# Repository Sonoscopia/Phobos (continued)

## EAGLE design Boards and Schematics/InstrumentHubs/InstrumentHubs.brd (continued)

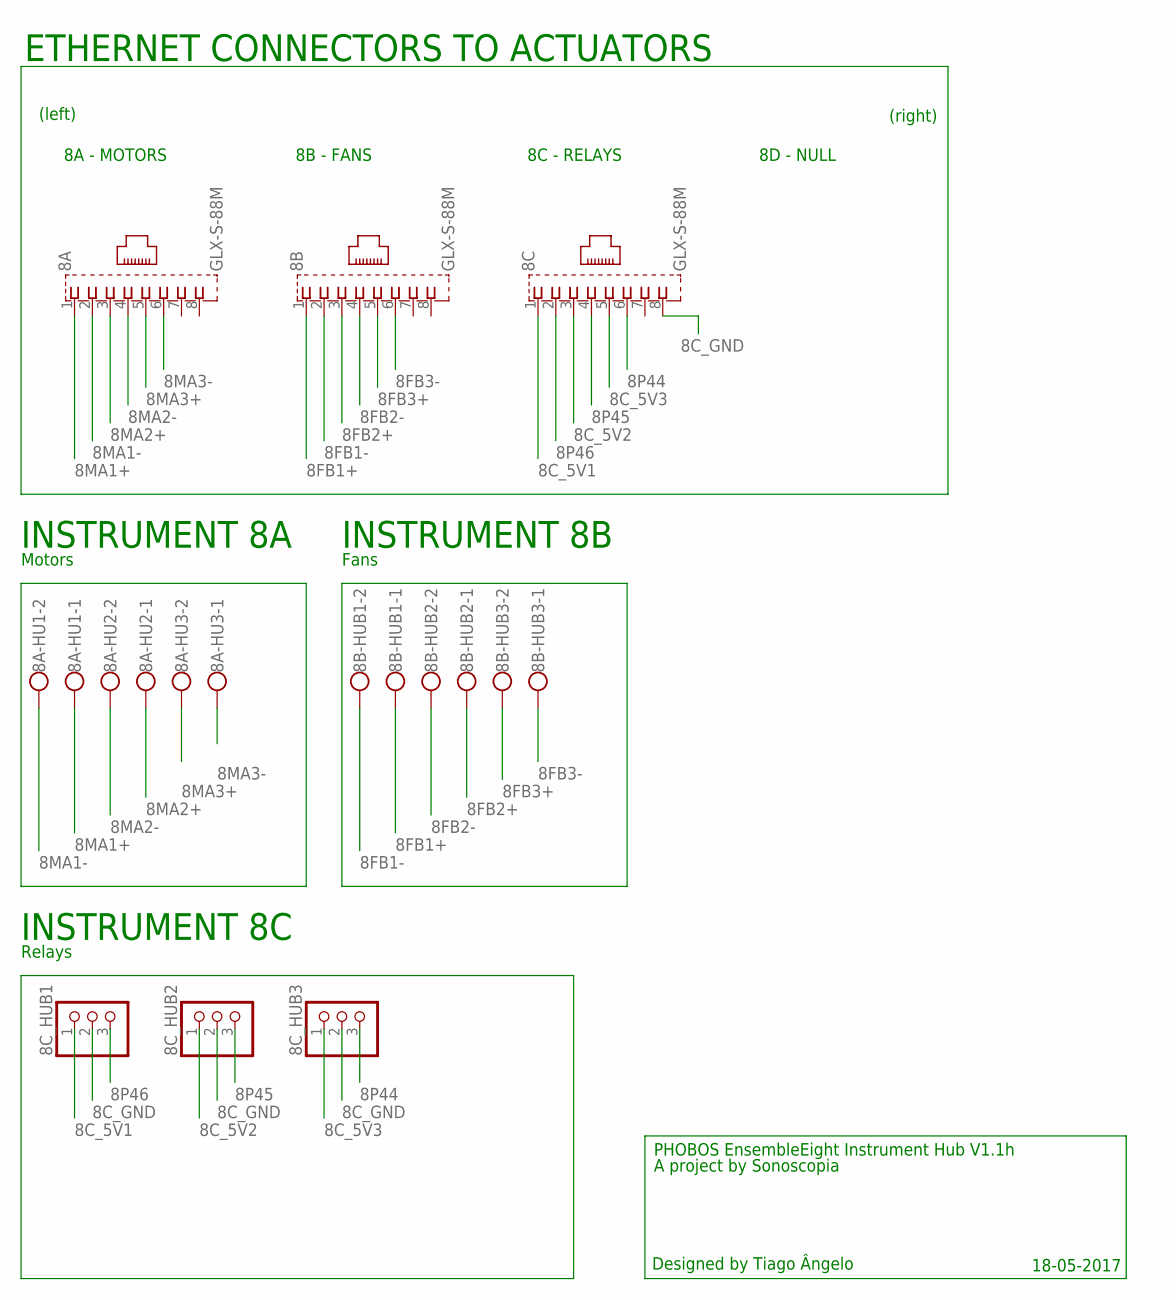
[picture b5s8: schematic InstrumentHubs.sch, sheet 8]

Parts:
8A, 8B, 8C: GLX-S-88M
8A-HU1, 8A-HU2, 8A-HU3, 8B-HUB1, 8B-HUB2, 8B-HUB3: W237-102
8C_HUB1, 8C_HUB2, 8C_HUB3: PINHD-1X3; 1X03

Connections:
8C_5V1: 8C.1, 8C_HUB1.1
8C_5V2: 8C.3, 8C_HUB2.1
8C_5V3: 8C.5, 8C_HUB3.1
8C_GND: 8C.8, 8C_HUB1.2, 8C_HUB2.2, 8C_HUB3.2
8FB1+: 8B.1, 8B-HUB1.1
8FB1-: 8B.2, 8B-HUB1.2
8FB2+: 8B.3, 8B-HUB2.1
8FB2-: 8B.4, 8B-HUB2.2
8FB3+: 8B.5, 8B-HUB3.2
8FB3-: 8B.6, 8B-HUB3.1
8MA1+: 8A.1, 8A-HU1.1
8MA1-: 8A.2, 8A-HU1.2
8MA2+: 8A.3, 8A-HU2.1
8MA2-: 8A.4, 8A-HU2.2
8MA3+: 8A.5, 8A-HU3.2
8MA3-: 8A.6, 8A-HU3.1
8P44: 8C.6, 8C_HUB3.3
8P45: 8C.4, 8C_HUB2.3
8P46: 8C.2, 8C_HUB1.3

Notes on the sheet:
INSTRUMENT 8A
PHOBOS EnsembleEight Instrument Hub V1.1h
Designed by Tiago Ângelo
A project by Sonoscopia
18-05-2017
Motors
INSTRUMENT 8B
Fans
INSTRUMENT 8C
Relays
(right)
(left)
ETHERNET CONNECTORS TO ACTUATORS
8D - NULL
8C - RELAYS
8B - FANS
8A - MOTORS

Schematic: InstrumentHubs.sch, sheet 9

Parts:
9A, 9B: GLX-S-88M
9A-HUB1, 9A-HUB2, 9A-HUB3, 9A-HUB4, 9B-HUB1, 9B-HUB2, 9B-HUB3: W237-102

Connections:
9LA1+: 9A.1, 9A-HUB1.1
9LA1-: 9A.2, 9A-HUB1.2
9LA2+: 9A.3, 9A-HUB2.1
9LA2-: 9A.4, 9A-HUB2.2
9LA3+: 9A.5, 9A-HUB3.2
9LA3-: 9A.6, 9A-HUB3.1
9LA4+: 9A.7, 9A-HUB4.2
9LA4-: 9A.8, 9A-HUB4.1
9LB1+: 9B.1, 9B-HUB1.1
9LB1-: 9B.2, 9B-HUB1.2
9LB2+: 9B.3, 9B-HUB2.1
9LB2-: 9B.4, 9B-HUB2.2
9LB3+: 9B.5, 9B-HUB3.2
9LB3-: 9B.6, 9B-HUB3.1

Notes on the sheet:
INSTRUMENT 9A
PHOBOS EnsembleNine Instrument Hub V1.1h
Designed by Tiago Ângelo
A project by Sonoscopia
Solenoid_valves_1
INSTRUMENT 9B
Solenoids_valves_2
18-05-2017
(right)
(left)
ETHERNET CONNECTORS TO ACTUATORS
9D - NULL
9C - NULL
9B - SOLENOIDS_VALVES_2
9A - SOLENOIDS_VALVES_1

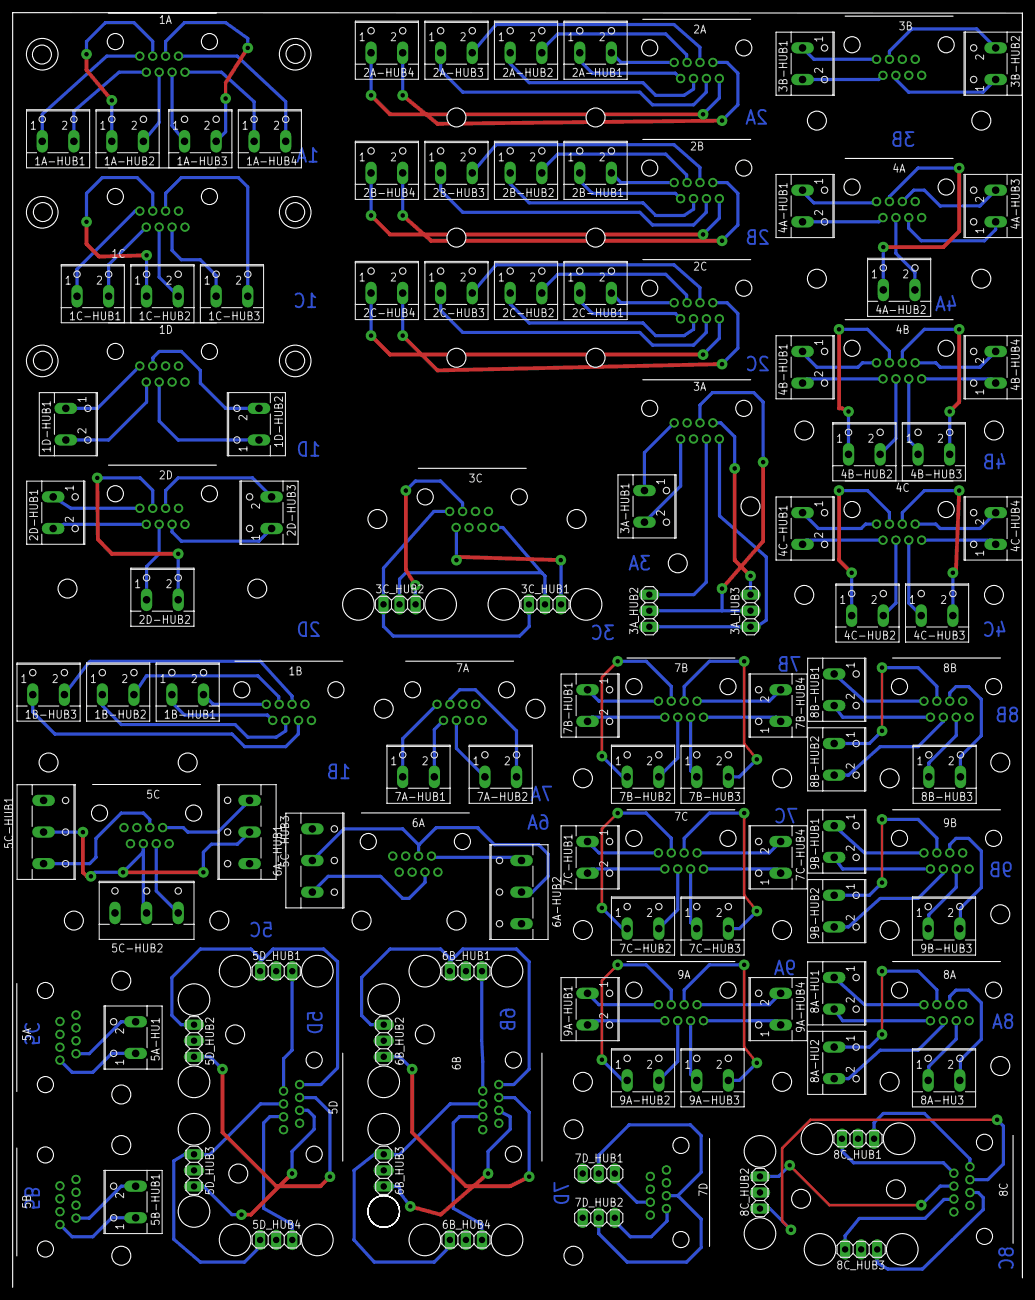
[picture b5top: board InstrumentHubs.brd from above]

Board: 2 copper layers, 159.7 x 201.6 mm, 117 parts (0 on the bottom side), 174 nets.

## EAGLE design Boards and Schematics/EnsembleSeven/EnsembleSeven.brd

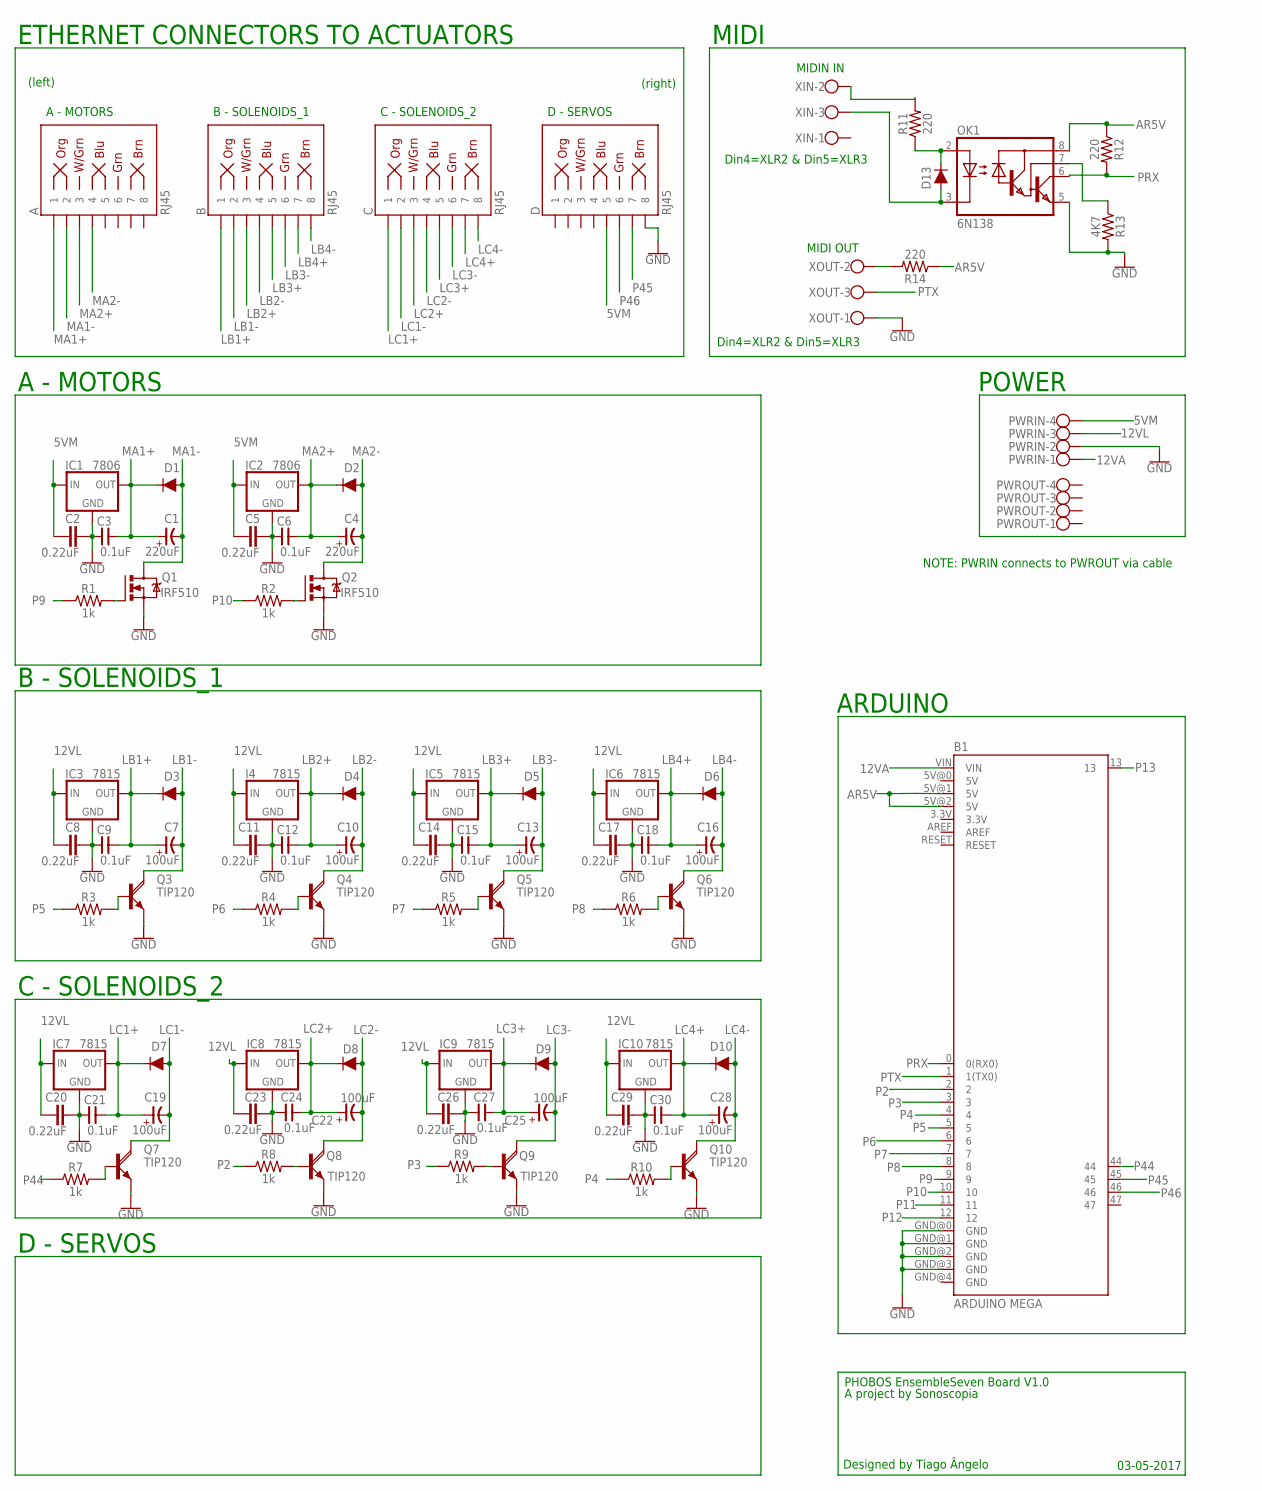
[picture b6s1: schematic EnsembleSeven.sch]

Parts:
A: RJ45; RJ45-8
B: RJ45; RJ45-8
B1: ARDUINO MEGA; ARDUINO_MEGA
C: RJ45; RJ45-8
C1, C4: 220uF; E-035X080
C2, C5, C8, C11, C14, C17, C20, C23, C26, C29: 0.22uF; C5B3
C3, C6, C9, C12, C15, C18, C21, C24, C27, C30: 0.1uF; C025-050X025
C7, C10, C13, C16, C19, C28: 100uF; CAP-MASTER_E-020X050
C22, C25: 100uF; E-020X050
D: RJ45; RJ45-8
D1, D2, D3, D4, D5, D6, D7, D8, D9, D10: 1A/50V/1.1V; DIODE-1N4001-KIT
D13: 200mA/100V/1V; DIODE-1N4148
I4: 7815; 78XXS
IC1, IC2: 7806; 78XXS
IC3, IC5, IC6, IC7, IC8, IC9, IC10: 7815; 78XXS
OK1: 6N138; DIL08
PWRIN: W237-4
PWROUT: W237-4
Q1, Q2: IRF510; TO220BV
Q3, Q4, Q5, Q6, Q7, Q10: TIP120; ROCKETFARM_TO220AV
Q8, Q9: TIP120; TO220AV
R1, R2, R3, R4, R5, R6, R7, R8, R9, R10: 1k; AXIAL-0.1
R11, R12, R14: 220; AXIAL-0.3
R13: 4K7; AXIAL-0.3
XIN: W237-103
XOUT: W237-103

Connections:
5VM: C2.1, C5.1, D.5, IC1.IN, IC2.IN, PWRIN.4
12VA: B1.VIN, PWRIN.1
12VL: C8.1, C11.1, C14.1, C17.1, C20.1, C23.1, C26.1, C29.1, I4.IN, IC3.IN, IC5.IN, IC6.IN, IC7.IN, IC8.IN, IC9.IN, IC10.IN, PWRIN.3
AR5V: B1.5V@1 (5V), B1.5V@2 (5V), OK1.8 (VCC), R12.P$1 (1), R14.P$1 (1)
GND: B1.GND@0 (GND), B1.GND@1 (GND), B1.GND@2 (GND), B1.GND@3 (GND), C2.2, C3.1, C5.2, C6.1, C8.2, C9.1, C11.2, C12.1, C14.2, C15.1, C17.2, C18.1, C20.2, C21.1, C23.2, C24.1, C26.2, C27.1, C29.2, C30.1, D.8, I4.GND, IC1.GND, IC2.GND, IC3.GND, IC5.GND, IC6.GND, IC7.GND, IC8.GND, IC9.GND, IC10.GND, OK1.5 (GND), PWRIN.2, Q1.S, Q2.S, Q3.E, Q4.E, Q5.E, Q6.E, Q7.E, Q8.E, Q9.E, Q10.E, R13.P$2 (2), XOUT.1
LB1+: B.1, C7.+, C9.2, D3.C, IC3.OUT
LB1-: B.2, C7.-, D3.A, Q3.C
LB2+: B.3, C10.+, C12.2, D4.C, I4.OUT
LB2-: B.4, C10.-, D4.A, Q4.C
LB3+: B.5, C13.+, C15.2, D5.C, IC5.OUT
LB3-: B.6, C13.-, D5.A, Q5.C
LB4+: B.7, C16.+, C18.2, D6.C, IC6.OUT
LB4-: B.8, C16.-, D6.A, Q6.C
LC1+: C.1, C19.+, C21.2, D7.C, IC7.OUT
LC1-: C.2, C19.-, D7.A, Q7.C
LC2+: C.3, C22.+, C24.2, D8.C, IC8.OUT
LC2-: C.4, C22.-, D8.A, Q8.C
LC3+: C.5, C25.+, C27.2, D9.C, IC9.OUT
LC3-: C.6, C25.-, D9.A, Q9.C
LC4+: C.7, C28.+, C30.2, D10.C, IC10.OUT
LC4-: C.8, C28.-, D10.A, Q10.C
MA1+: A.1, C1.+, C3.2, D1.C, IC1.OUT
MA1-: A.2, C1.-, D1.A, Q1.D
MA2+: A.3, C4.+, C6.2, D2.C, IC2.OUT
MA2-: A.4, C4.-, D2.A, Q2.D
unnamed: Q5.B, R5.P$2 (2)
unnamed: R14.P$2 (2), XOUT.2
unnamed: Q6.B, R6.P$2 (2)
unnamed: Q9.B, R9.P$2 (2)
unnamed: Q8.B, R8.P$2 (2)
unnamed: Q1.G, R1.P$2 (2)
unnamed: Q2.G, R2.P$2 (2)
unnamed: Q10.B, R10.P$2 (2)
unnamed: Q3.B, R3.P$2 (2)
unnamed: Q4.B, R4.P$2 (2)
unnamed: Q7.B, R7.P$2 (2)
unnamed: D13.A, OK1.3 (C), XIN.3
unnamed: D13.C, OK1.2 (A), R11.P$1 (1)
unnamed: R11.P$2 (2), XIN.2
unnamed: OK1.7 (VB), R13.P$1 (1)
P2: B1.2, R8.P$1 (1)
P3: B1.3, R9.P$1 (1)
P4: B1.4, R10.P$1 (1)
P5: B1.5, R3.P$1 (1)
P6: B1.6, R4.P$1 (1)
P7: B1.7, R5.P$1 (1)
P8: B1.8, R6.P$1 (1)
P9: B1.9, R1.P$1 (1)
P10: B1.10, R2.P$1 (1)
P11: B1.11
P12: B1.12
P13: B1.13
P44: B1.44, R7.P$1 (1)
P45: B1.45, D.7
P46: B1.46, D.6
PRX: B1.0 (0(RX0)), OK1.6 (VO), R12.P$2 (2)
PTX: B1.1 (1(TX0)), XOUT.3

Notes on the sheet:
Din4=XLR2 & Din5=XLR3
MIDI OUT
MIDIN IN
POWER
MIDI
ARDUINO
(right)
(left)
ETHERNET CONNECTORS TO ACTUATORS
D - SERVOS
C - SOLENOIDS_2
B - SOLENOIDS_1
A - MOTORS
PHOBOS EnsembleSeven Board V1.0
Designed by Tiago Ângelo
A project by Sonoscopia
03-05-2017
NOTE: PWRIN connects to PWROUT via cable

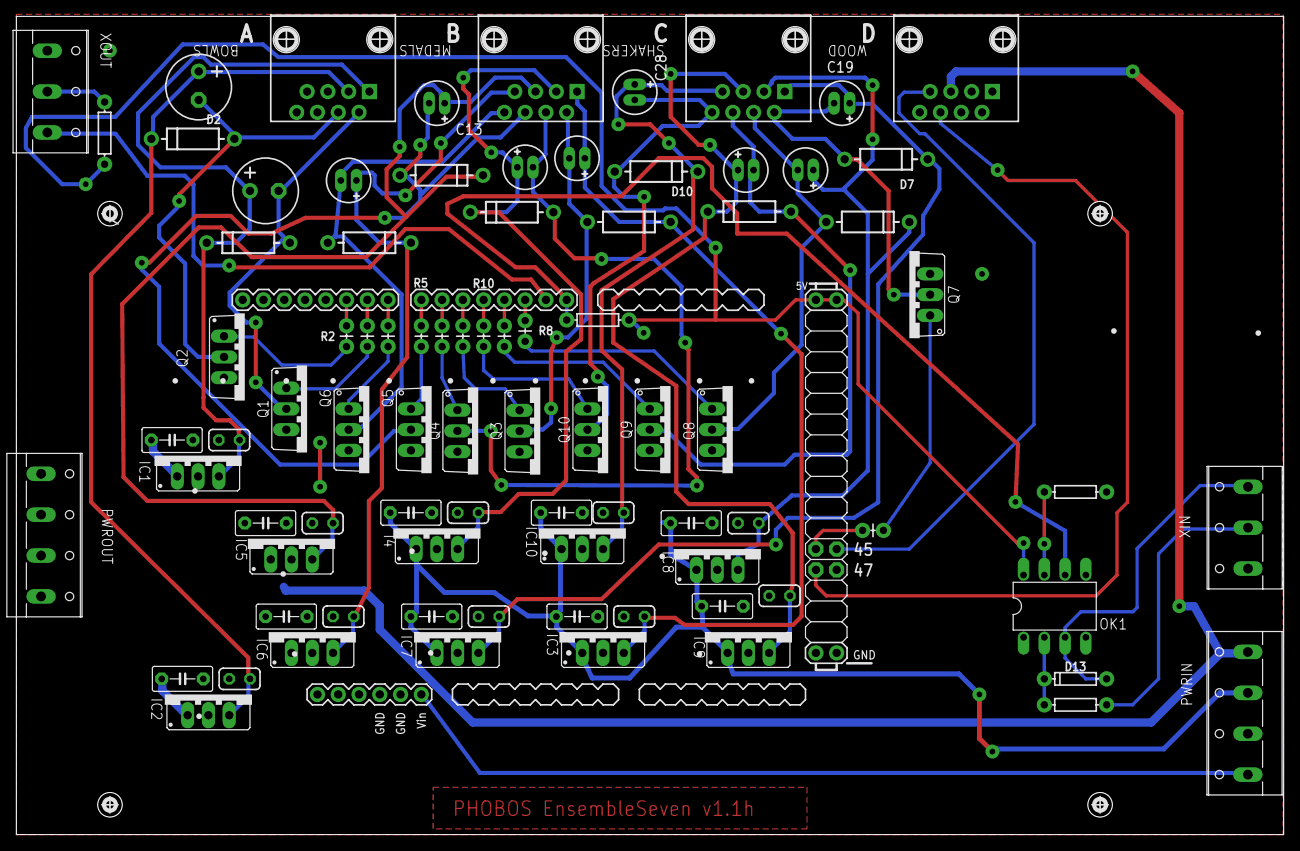
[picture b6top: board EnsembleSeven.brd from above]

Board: 2 copper layers, 155.0 x 100.1 mm, 85 parts (0 on the bottom side), 54 nets.

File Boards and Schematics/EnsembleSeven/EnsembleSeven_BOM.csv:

Partlist exported from C:/Users/tiago/Documents/eagle/PHOBOS/EnsembleSeven/EnsembleSeven.sch at 15-05-2017 22:23

Qty Value         Device                  Package              Parts                                         Description               MF                MPN     OC_FARNELL OC_NEWARK PROD_ID    SF_ID     VALUE        
2                 W237-103                W237-103             XIN, XOUT                                     WAGO SCREW CLAMP                            237-103 unknown    18M7116                                     
2                 W237-4                  W237-4               PWRIN, PWROUT                                 WAGO SCREW CLAMP                                    unknown    unknown                                     
10  0.1uF         CNP-C025-050X025        C025-050X025         C3, C6, C9, C12, C15, C18, C21, C24, C27, C30 NON-POLARIZED CAP                                                                                          
10  0.22uF        C5/3                    C5B3                 C2, C5, C8, C11, C14, C17, C20, C23, C26, C29 CAPACITOR                                                                                                  
6   100uF         CAP-MASTER_CP-E-020X050 CAP-MASTER_E-020X050 C7, C10, C13, C16, C19, C28                   POLARIZED CAP                                                                                              
2   100uF         CP-E-020X050            E-020X050            C22, C25                                      POLARIZED CAP                                                                                              
10  1A/50V/1.1V   DIODE-KIT2              DIODE-1N4001-KIT     D1, D2, D3, D4, D5, D6, D7, D8, D9, D10       Diode                                                                    DIO-09176            1A/50V/1.1V  
10  1k            1KOHM-VERT-1/4W-1%      AXIAL-0.1            R1, R2, R3, R4, R5, R6, R7, R8, R9, R10       1kO resistor                                                             RES-12182            1k           
1   200mA/100V/1V DIODE-1N4148            DIODE-1N4148         D13                                           Diode                                                                    DIO-08378            200mA/100V/1V
3   220           1KOHM-HORIZ-1/4W-5%     AXIAL-0.3            R11, R12, R14                                 1kO resistor                                                             RES-08380            1k           
2   220uF         CP-E-035X080            E-035X080            C1, C4                                        POLARIZED CAP                                                                                              
1   4K7           1KOHM-HORIZ-1/4W-5%     AXIAL-0.3            R13                                           1kO resistor                                                             RES-08380            1k           
1   6N138         6N138                   DIL08                OK1                                           MOTOROLA OPTO COUPLER     VISHAY/TELEFUNKEN 6N138   9860150    35K5294                                     
2   7806          78XXS                   78XXS                IC1, IC2                                      VOLTAGE REGULATOR                                                                                          
8   7815          78XXS                   78XXS                I4, IC3, IC5, IC6, IC7, IC8, IC9, IC10        VOLTAGE REGULATOR                                                                                          
1   ARDUINO MEGA  ARDUINO_MEGA_R3FULL     ARDUINO_MEGA         B1                                            Arduino Mega R3                                                                                            
2   IRF510        IRF520                  TO220BV              Q1, Q2                                        HEXFET Power MOSFET                                                                                        
4   RJ45          RJ45-8                  RJ45-8               A, B, C, D                                    RJ45 Jack - 8 pin                                                        CONN-08506 PRT-00643 RJ45         
6   TIP120        ROCKETFARM_TIP120V      ROCKETFARM_TO220AV   Q3, Q4, Q5, Q6, Q7, Q10                       NPN DARLINGTON TRANSISTOR                                                                                  
2   TIP120        TIP120V                 TO220AV              Q8, Q9                                        NPN DARLINGTON TRANSISTOR

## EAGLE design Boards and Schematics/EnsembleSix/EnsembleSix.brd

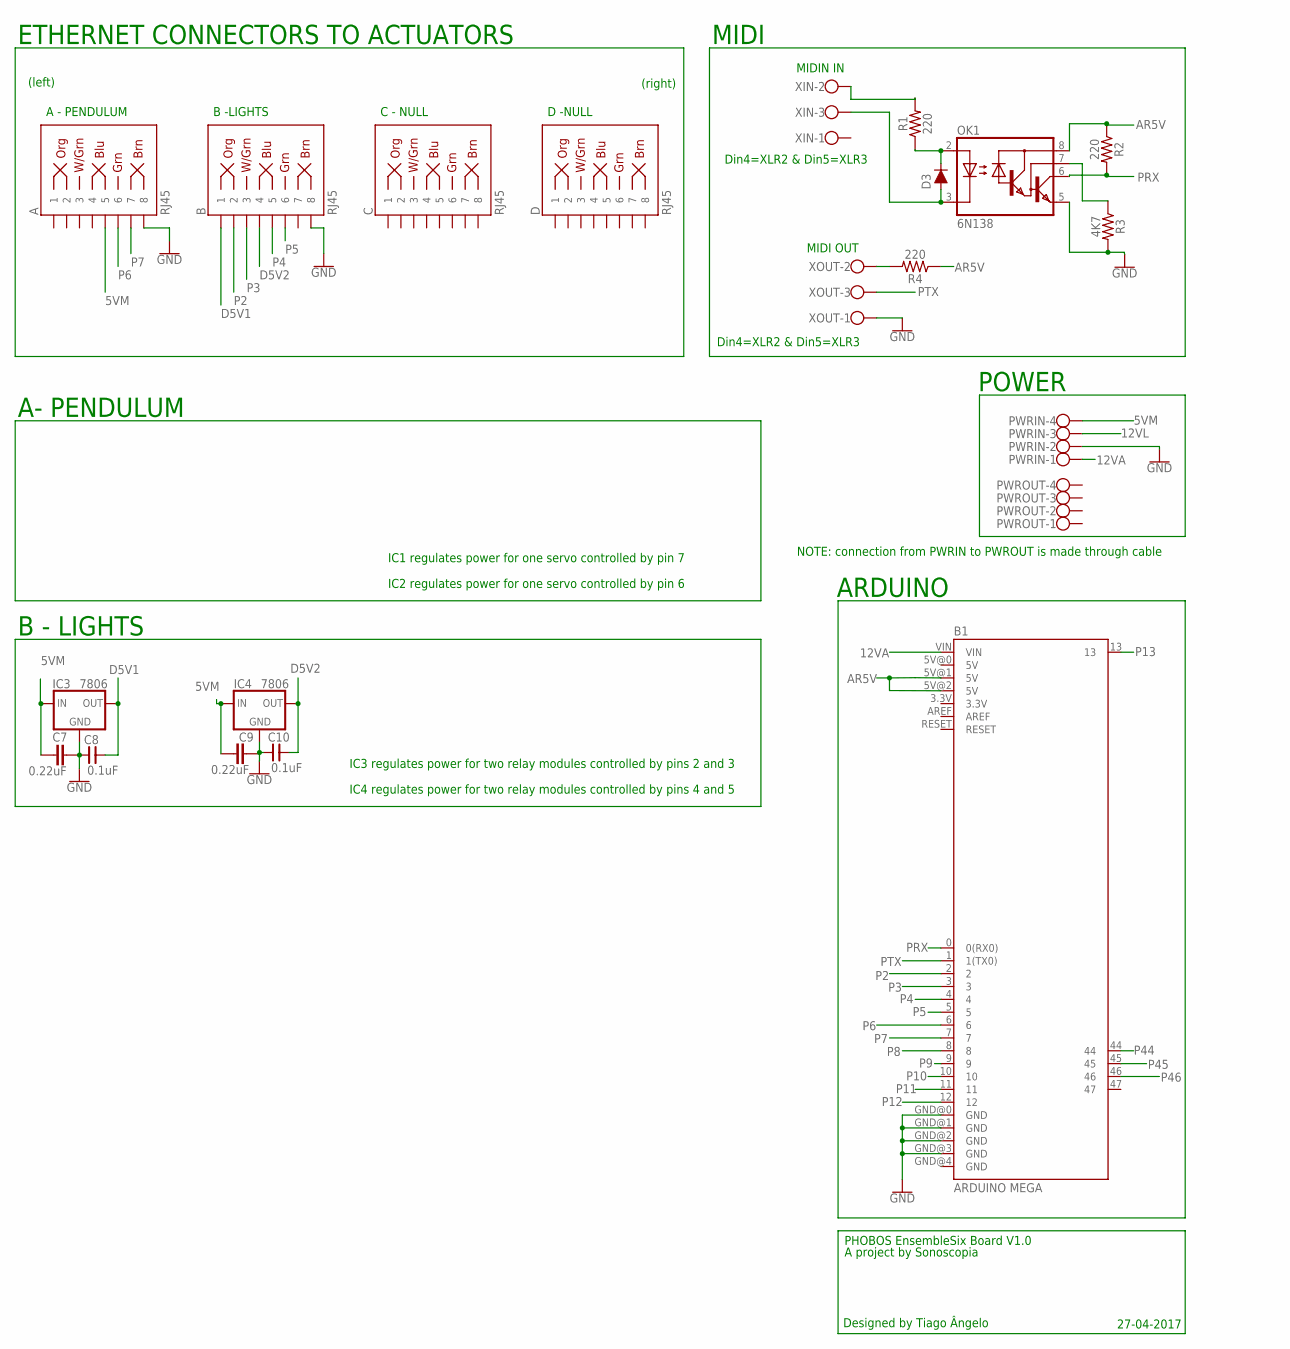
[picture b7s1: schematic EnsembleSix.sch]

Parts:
A: RJ45; RJ45-8
B: RJ45; RJ45-8
B1: ARDUINO MEGA; ARDUINO_MEGA
C: RJ45; RJ45-8
C7, C9: 0.22uF; C5B3
C8, C10: 0.1uF; C025-050X025
D: RJ45; RJ45-8
D3: 200mA/100V/1V; DIODE-1N4148
IC3, IC4: 7806; 78XXS
OK1: 6N138; DIL08
PWRIN: W237-4
PWROUT: W237-4
R1, R2, R4: 220; AXIAL-0.3
R3: 4K7; AXIAL-0.3
XIN: W237-103
XOUT: W237-103

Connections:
5VM: A.5, C7.1, C9.1, IC3.IN, IC4.IN, PWRIN.4
12VA: B1.VIN, PWRIN.1
12VL: PWRIN.3
AR5V: B1.5V@1 (5V), B1.5V@2 (5V), OK1.8 (VCC), R2.P$1 (1), R4.P$1 (1)
D5V1: B.1, C8.2, IC3.OUT
D5V2: B.4, C10.2, IC4.OUT
GND: A.8, B.8, B1.GND@0 (GND), B1.GND@1 (GND), B1.GND@2 (GND), B1.GND@3 (GND), C7.2, C8.1, C9.2, C10.1, IC3.GND, IC4.GND, OK1.5 (GND), PWRIN.2, R3.P$2 (2), XOUT.1
unnamed: R4.P$2 (2), XOUT.2
unnamed: D3.A, OK1.3 (C), XIN.3
unnamed: D3.C, OK1.2 (A), R1.P$1 (1)
unnamed: R1.P$2 (2), XIN.2
unnamed: OK1.7 (VB), R3.P$1 (1)
P2: B.2, B1.2
P3: B.3, B1.3
P4: B.5, B1.4
P5: B.6, B1.5
P6: A.6, B1.6
P7: A.7, B1.7
P8: B1.8
P9: B1.9
P10: B1.10
P11: B1.11
P12: B1.12
P13: B1.13
P44: B1.44
P45: B1.45
P46: B1.46
PRX: B1.0 (0(RX0)), OK1.6 (VO), R2.P$2 (2)
PTX: B1.1 (1(TX0)), XOUT.3

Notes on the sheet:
Din4=XLR2 & Din5=XLR3
MIDI OUT
MIDIN IN
POWER
MIDI
ARDUINO
(right)
(left)
ETHERNET CONNECTORS TO ACTUATORS
D -NULL
C - NULL
B -LIGHTS
A - PENDULUM
A- PENDULUM
PHOBOS EnsembleSix Board V1.0
Designed by Tiago Ângelo
A project by Sonoscopia
27-04-2017
B - LIGHTS
IC1 regulates power for one servo controlled by pin 7
IC2 regulates power for one servo controlled by pin 6
IC3 regulates power for two relay modules controlled by pins 2 and 3
IC4 regulates power for two relay modules controlled by pins 4 and 5
NOTE: connection from PWRIN to PWROUT is made through cable

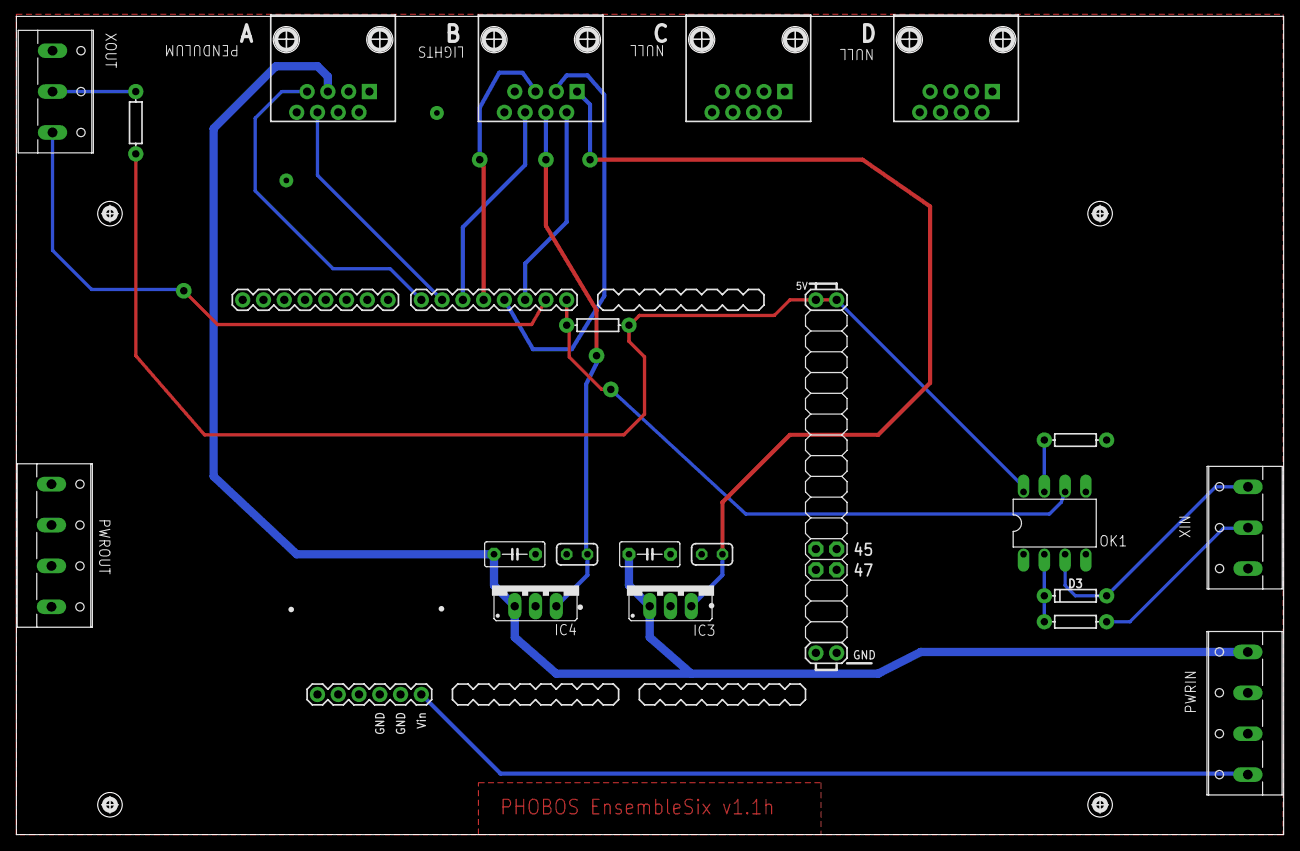
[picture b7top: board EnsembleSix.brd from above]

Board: 2 copper layers, 155.0 x 100.1 mm, 21 parts (0 on the bottom side), 19 nets.

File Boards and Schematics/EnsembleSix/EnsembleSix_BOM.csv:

Partlist exported from C:/Users/tiago/Documents/eagle/PHOBOS/EnsembleSix/EnsembleSix.sch at 15-05-2017 21:26

Qty Value         Device              Package      Parts         Description           MF                MPN     OC_FARNELL OC_NEWARK PROD_ID    SF_ID     VALUE        
2                 W237-103            W237-103     XIN, XOUT     WAGO SCREW CLAMP                        237-103 unknown    18M7116                                     
2                 W237-4              W237-4       PWRIN, PWROUT WAGO SCREW CLAMP                                unknown    unknown                                     
2   0.1uF         CNP-C025-050X025    C025-050X025 C8, C10       NON-POLARIZED CAP                                                                                      
2   0.22uF        C5/3                C5B3         C7, C9        CAPACITOR                                                                                              
1   200mA/100V/1V DIODE-1N4148        DIODE-1N4148 D3            Diode                                                                DIO-08378            200mA/100V/1V
3   220           1KOHM-HORIZ-1/4W-5% AXIAL-0.3    R1, R2, R4    1kO resistor                                                         RES-08380            1k           
1   4K7           1KOHM-HORIZ-1/4W-5% AXIAL-0.3    R3            1kO resistor                                                         RES-08380            1k           
1   6N138         6N138               DIL08        OK1           MOTOROLA OPTO COUPLER VISHAY/TELEFUNKEN 6N138   9860150    35K5294                                     
2   7806          78XXS               78XXS        IC3, IC4      VOLTAGE REGULATOR                                                                                      
1   ARDUINO MEGA  ARDUINO_MEGA_R3FULL ARDUINO_MEGA B1            Arduino Mega R3                                                                                        
4   RJ45          RJ45-8              RJ45-8       A, B, C, D    RJ45 Jack - 8 pin                                                    CONN-08506 PRT-00643 RJ45

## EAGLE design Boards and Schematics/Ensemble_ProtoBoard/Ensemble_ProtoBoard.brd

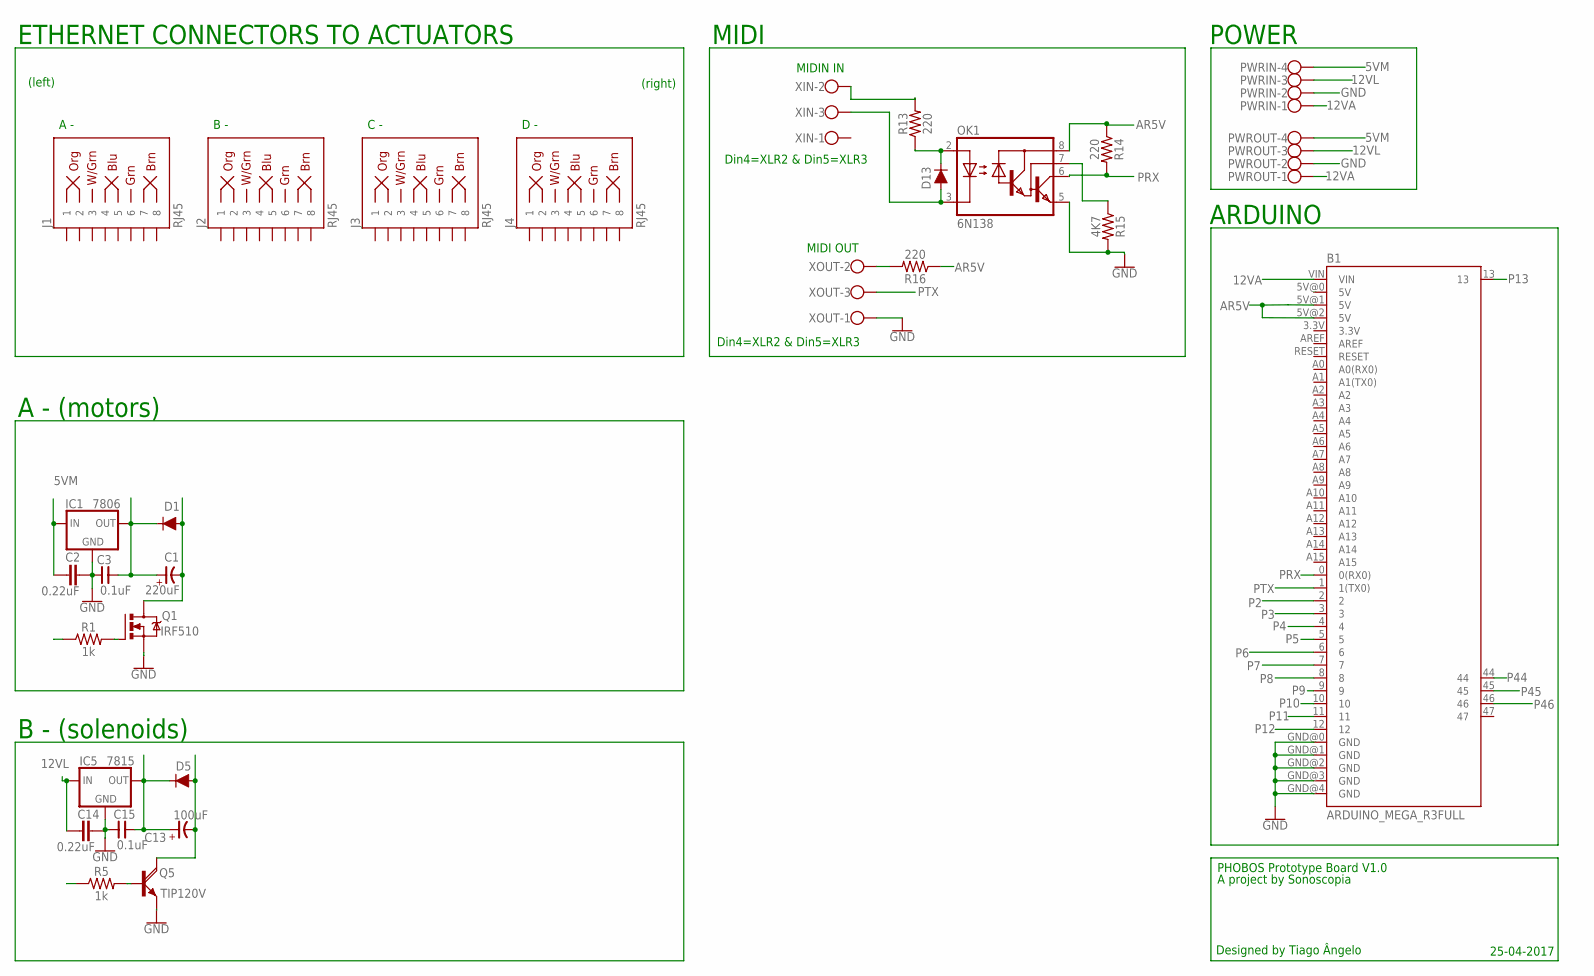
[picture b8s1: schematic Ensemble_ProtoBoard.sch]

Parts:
B1: ARDUINO_MEGA_R3FULL; ARDUINO_MEGA
C1: 220uF; E-035X080
C2, C14: 0.22uF; C5B3
C3, C15: 0.1uF; C025-050X025
C13: 100uF; E-020X050
D1, D5: 1A/50V/1.1V; DIODE-1N4001-KIT
D13: 200mA/100V/1V; DIODE-1N4148
IC1: 7806; 78XXS
IC5: 7815; 78XXS
J1, J2, J3, J4: RJ45; RJ45-8
OK1: 6N138; DIL08
PWRIN: W237-4
PWROUT: W237-4
Q1: IRF510; TO220BV
Q5: TIP120V; TO220AV
R1, R5: 1k; AXIAL-0.1
R13, R14, R16: 220; AXIAL-0.3
R15: 4K7; AXIAL-0.3
XIN: W237-103
XOUT: W237-103

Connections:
5VM: C2.1, IC1.IN, PWRIN.4, PWROUT.4
12VA: B1.VIN, PWRIN.1, PWROUT.1
12VL: C14.1, IC5.IN, PWRIN.3, PWROUT.3
AR5V: B1.5V@1 (5V), B1.5V@2 (5V), OK1.8 (VCC), R14.P$1 (1), R16.P$1 (1)
GND: B1.GND@0 (GND), B1.GND@1 (GND), B1.GND@2 (GND), B1.GND@3 (GND), B1.GND@4 (GND), C2.2, C3.1, C14.2, C15.1, IC1.GND, IC5.GND, OK1.5 (GND), PWRIN.2, PWROUT.2, Q1.S, Q5.E, R15.P$2 (2), XOUT.1
unnamed: C1.+, C3.2, D1.C, IC1.OUT, Q1.G, R1.P$2 (2)
unnamed: C1.-, D1.A, Q1.D, R16.P$2 (2), XOUT.2
unnamed: C13.+, C15.2, D5.C, IC5.OUT
unnamed: C13.-, D5.A, Q5.C
unnamed: Q5.B, R5.P$2 (2)
unnamed: D13.A, OK1.3 (C), XIN.3
unnamed: D13.C, OK1.2 (A), R13.P$1 (1)
unnamed: R13.P$2 (2), XIN.2
unnamed: OK1.7 (VB), R15.P$1 (1)
P2: B1.2
P3: B1.3
P4: B1.4
P5: B1.5
P6: B1.6
P7: B1.7
P8: B1.8
P9: B1.9
P10: B1.10
P11: B1.11
P12: B1.12
P13: B1.13
P44: B1.44
P45: B1.45
P46: B1.46
PRX: B1.0 (0(RX0)), OK1.6 (VO), R14.P$2 (2)
PTX: B1.1 (1(TX0)), XOUT.3

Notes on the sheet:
Din4=XLR2 & Din5=XLR3
MIDI OUT
MIDIN IN
POWER
MIDI
ARDUINO
(right)
(left)
ETHERNET CONNECTORS TO ACTUATORS
A -
B -
C -
D -
A - (motors)
B - (solenoids)
PHOBOS Prototype Board V1.0
Designed by Tiago Ângelo
A project by Sonoscopia
25-04-2017

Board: 2 copper layers, 29 parts (0 on the bottom side), 16 nets, no tracks yet.

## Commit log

2016-12-13 Uploaded gitignore
2016-12-13 Upload example#1 - robot afraid of light
2017-03-15 Prototype board - First draft
2017-05-16 Rename Icon to Icon
2017-05-16 upload...
2017-05-26 Firmware draft
2017-05-27 MIDI and POWER diagram
2017-05-27 EnsembleOne firmware
2017-05-27 added "Icon" to gitignore since Windows doesn't like them
2017-05-27 gitignore
2017-05-27 gtignore minor change
2017-05-27 updated version number
2017-05-27 Max patch to test all ensembles and program servos
2017-05-27 added MIDI thru
2017-05-27 Upload ensemble two firmeware
2017-05-27 better description
2017-05-27 added servo increment programmer
2017-05-27 minor fix
2017-05-27 uploaded ensemble three firmeware
2017-05-27 reorganized folder
2017-05-27 set relays to off state at startup
2017-05-27 uploaded ensemble four firmeware
2017-05-27 updated servo programmer
    added min/max increments which relate to the servo speed
2017-05-27 minor fix
    added break after noteOn received
2017-05-27 Uploaded ensemble five firmware
2017-05-27 minor change
2017-05-27 update ensemble six firmware
2017-05-27 added servo programmer for ensemble six
2017-05-27 uploaded ensemble seven firmware
2017-05-27 added servo programmer for ensemble seven
2017-05-27 correct pin numbers according to datasheet
2017-05-27 uploaded ensemble eight firmware
2017-05-27 correct pin output according to datasheet
2017-05-27 uploaded ensemble nine firmeware
2017-05-31 several fixes
2017-05-31 added examples
2017-05-31 added servo programmer
2017-05-31 added utilities
2017-05-31 Ableton Tester
2017-06-01 added utility to remap notes if necessary
2017-06-01 Fixed servo issue
    servos were continuously trying to go to 0º
2017-06-01 Fixed servo issue
2017-06-02 fixed servo issues
2017-06-02 callibrating through midi cc now changes the servo position on the fly
2017-06-20 added simple m4l utility to remap notes
2017-06-20 changed all ensemble to MIDI channel 1
    all actuators are mapped with chromatic notes on channel 1
2017-06-20 changed servo programmer to comply with a single MIDI channel
2017-06-26 Several fixes
    note2pin array size fixes
    other minor fixes
2017-06-26 added M4L midi generators to play the robot
2017-06-26 Added MakeyMakey MIDI interface
2025-08-14 Update LICENSE
2025-08-14 added schematics, boards and BOM's
2025-08-14 added note mapping
2025-08-14 updated gitignore
